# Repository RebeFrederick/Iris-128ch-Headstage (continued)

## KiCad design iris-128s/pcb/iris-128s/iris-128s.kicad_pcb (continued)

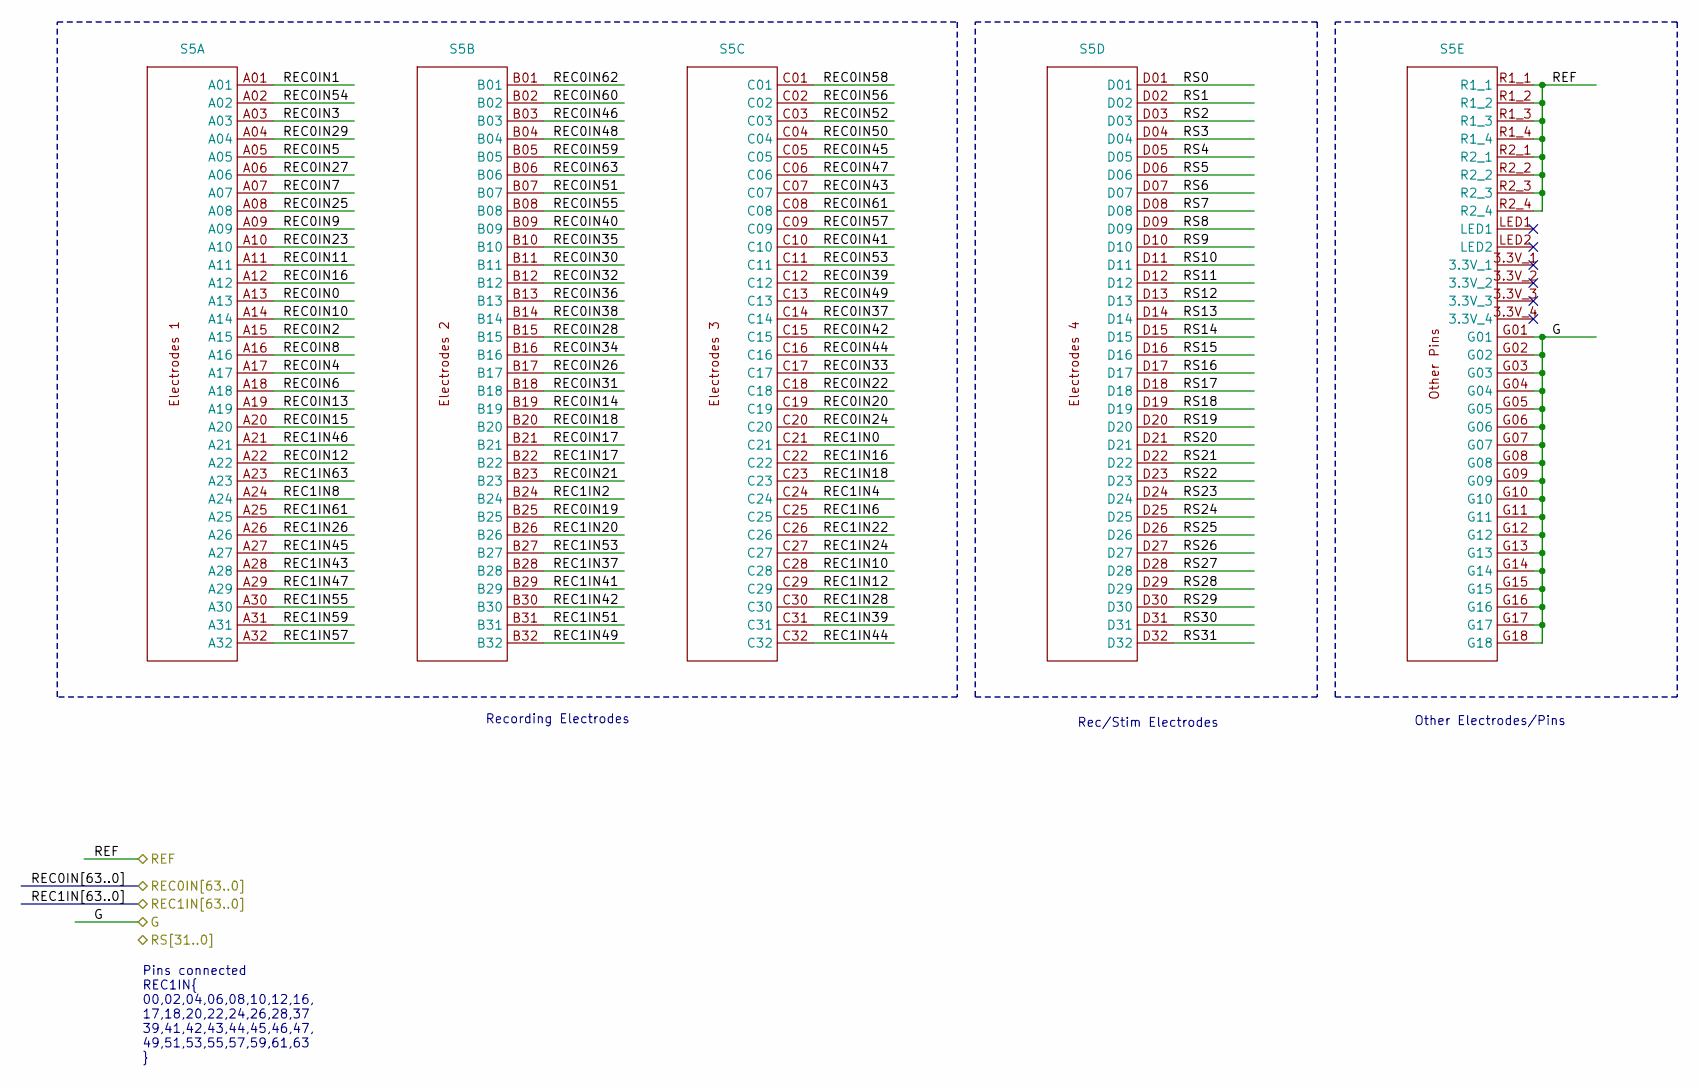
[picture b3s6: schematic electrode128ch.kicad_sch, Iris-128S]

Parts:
S5: SAMTEC_SEAM8-20-S02.0-X-08-3_Cereplex; MPN SEAM8-20-S02.0-S-08-3

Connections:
/REC0IN0: S5.A13; also elsewhere on the board
/REC0IN1: S5.A01; also elsewhere on the board
/REC0IN2: S5.A15; also elsewhere on the board
/REC0IN3: S5.A03; also elsewhere on the board
/REC0IN4: S5.A17; also elsewhere on the board
/REC0IN5: S5.A05; also elsewhere on the board
/REC0IN6: S5.A18; also elsewhere on the board
/REC0IN7: S5.A07; also elsewhere on the board
/REC0IN8: S5.A16; also elsewhere on the board
/REC0IN9: S5.A09; also elsewhere on the board
/REC0IN10: S5.A14; also elsewhere on the board
/REC0IN11: S5.A11; also elsewhere on the board
/REC0IN12: S5.A22; also elsewhere on the board
/REC0IN13: S5.A19; also elsewhere on the board
/REC0IN14: S5.B19; also elsewhere on the board
/REC0IN15: S5.A20; also elsewhere on the board
/REC0IN16: S5.A12; also elsewhere on the board
/REC0IN17: S5.B21; also elsewhere on the board
/REC0IN18: S5.B20; also elsewhere on the board
/REC0IN19: S5.B25; also elsewhere on the board
/REC0IN20: S5.C19; also elsewhere on the board
/REC0IN21: S5.B23; also elsewhere on the board
/REC0IN22: S5.C18; also elsewhere on the board
/REC0IN23: S5.A10; also elsewhere on the board
/REC0IN24: S5.C20; also elsewhere on the board
/REC0IN25: S5.A08; also elsewhere on the board
/REC0IN26: S5.B17; also elsewhere on the board
/REC0IN27: S5.A06; also elsewhere on the board
/REC0IN28: S5.B15; also elsewhere on the board
/REC0IN29: S5.A04; also elsewhere on the board
/REC0IN30: S5.B11; also elsewhere on the board
/REC0IN31: S5.B18; also elsewhere on the board
/REC0IN32: S5.B12; also elsewhere on the board
/REC0IN33: S5.C17; also elsewhere on the board
/REC0IN34: S5.B16; also elsewhere on the board
/REC0IN35: S5.B10; also elsewhere on the board
/REC0IN36: S5.B13; also elsewhere on the board
/REC0IN37: S5.C14; also elsewhere on the board
/REC0IN38: S5.B14; also elsewhere on the board
/REC0IN39: S5.C12; also elsewhere on the board
/REC0IN40: S5.B09; also elsewhere on the board
/REC0IN41: S5.C10; also elsewhere on the board
/REC0IN42: S5.C15; also elsewhere on the board
/REC0IN43: S5.C07; also elsewhere on the board
/REC0IN44: S5.C16; also elsewhere on the board
/REC0IN45: S5.C05; also elsewhere on the board
/REC0IN46: S5.B03; also elsewhere on the board
/REC0IN47: S5.C06; also elsewhere on the board
/REC0IN48: S5.B04; also elsewhere on the board
/REC0IN49: S5.C13; also elsewhere on the board
/REC0IN50: S5.C04; also elsewhere on the board
/REC0IN51: S5.B07; also elsewhere on the board
/REC0IN52: S5.C03; also elsewhere on the board
/REC0IN53: S5.C11; also elsewhere on the board
/REC0IN54: S5.A02; also elsewhere on the board
/REC0IN55: S5.B08; also elsewhere on the board
/REC0IN56: S5.C02; also elsewhere on the board
/REC0IN57: S5.C09; also elsewhere on the board
/REC0IN58: S5.C01; also elsewhere on the board
/REC0IN59: S5.B05; also elsewhere on the board
/REC0IN60: S5.B02; also elsewhere on the board
/REC0IN61: S5.C08; also elsewhere on the board
/REC0IN62: S5.B01; also elsewhere on the board
/REC0IN63: S5.B06; also elsewhere on the board
/REC1IN0: S5.C21; also elsewhere on the board
/REC1IN2: S5.B24; also elsewhere on the board
/REC1IN4: S5.C24; also elsewhere on the board
/REC1IN6: S5.C25; also elsewhere on the board
/REC1IN8: S5.A24; also elsewhere on the board
/REC1IN10: S5.C28; also elsewhere on the board
/REC1IN12: S5.C29; also elsewhere on the board
/REC1IN16: S5.C22; also elsewhere on the board
/REC1IN17: S5.B22; also elsewhere on the board
/REC1IN18: S5.C23; also elsewhere on the board
/REC1IN20: S5.B26; also elsewhere on the board
/REC1IN22: S5.C26; also elsewhere on the board
/REC1IN24: S5.C27; also elsewhere on the board
/REC1IN26: S5.A26; also elsewhere on the board
/REC1IN28: S5.C30; also elsewhere on the board
/REC1IN37: S5.B28; also elsewhere on the board
/REC1IN39: S5.C31; also elsewhere on the board
/REC1IN41: S5.B29; also elsewhere on the board
/REC1IN42: S5.B30; also elsewhere on the board
/REC1IN43: S5.A28; also elsewhere on the board
/REC1IN44: S5.C32; also elsewhere on the board
/REC1IN45: S5.A27; also elsewhere on the board
/REC1IN46: S5.A21; also elsewhere on the board
/REC1IN47: S5.A29; also elsewhere on the board
/REC1IN49: S5.B32; also elsewhere on the board
/REC1IN51: S5.B31; also elsewhere on the board
/REC1IN53: S5.B27; also elsewhere on the board
/REC1IN55: S5.A30; also elsewhere on the board
/REC1IN57: S5.A32; also elsewhere on the board
/REC1IN59: S5.A31; also elsewhere on the board
/REC1IN61: S5.A25; also elsewhere on the board
/REC1IN63: S5.A23; also elsewhere on the board
/REF_ELEC: S5.R1_1, S5.R1_2, S5.R1_3, S5.R1_4, S5.R2_1, S5.R2_2, S5.R2_3, S5.R2_4; also elsewhere on the board
/RS0: S5.D01; also elsewhere on the board
/RS1: S5.D02; also elsewhere on the board
/RS2: S5.D03; also elsewhere on the board
/RS3: S5.D04; also elsewhere on the board
/RS4: S5.D05; also elsewhere on the board
/RS5: S5.D06; also elsewhere on the board
/RS6: S5.D07; also elsewhere on the board
/RS7: S5.D08; also elsewhere on the board
/RS8: S5.D09; also elsewhere on the board
/RS9: S5.D10; also elsewhere on the board
/RS10: S5.D11; also elsewhere on the board
/RS11: S5.D12; also elsewhere on the board
/RS12: S5.D13; also elsewhere on the board
/RS13: S5.D14; also elsewhere on the board
/RS14: S5.D15; also elsewhere on the board
/RS15: S5.D16; also elsewhere on the board
/RS16: S5.D17; also elsewhere on the board
/RS17: S5.D18; also elsewhere on the board
/RS18: S5.D19; also elsewhere on the board
/RS19: S5.D20; also elsewhere on the board
/RS20: S5.D21; also elsewhere on the board
/RS21: S5.D22; also elsewhere on the board
/RS22: S5.D23; also elsewhere on the board
/RS23: S5.D24; also elsewhere on the board
/RS24: S5.D25; also elsewhere on the board
/RS25: S5.D26; also elsewhere on the board
/RS26: S5.D27; also elsewhere on the board
/RS27: S5.D28; also elsewhere on the board
/RS28: S5.D29; also elsewhere on the board
/RS29: S5.D30; also elsewhere on the board
/RS30: S5.D31; also elsewhere on the board
/RS31: S5.D32; also elsewhere on the board
GND1: S5.G01, S5.G02, S5.G03, S5.G04, S5.G05, S5.G06, S5.G07, S5.G08, S5.G09, S5.G10, S5.G11, S5.G12, S5.G13, S5.G14, S5.G15, S5.G16, S5.G17, S5.G18; also elsewhere on the board

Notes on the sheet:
Pins connected REC1IN{ 00,02,04,06,08,10,12,16, 17,18,20,22,24,26,28,37 39,41,42,43,44,45,46,47, 49,51,53,55,57,59,61,63 }
Rec/Stim Electrodes
Other Electrodes/Pins
Recording Electrodes

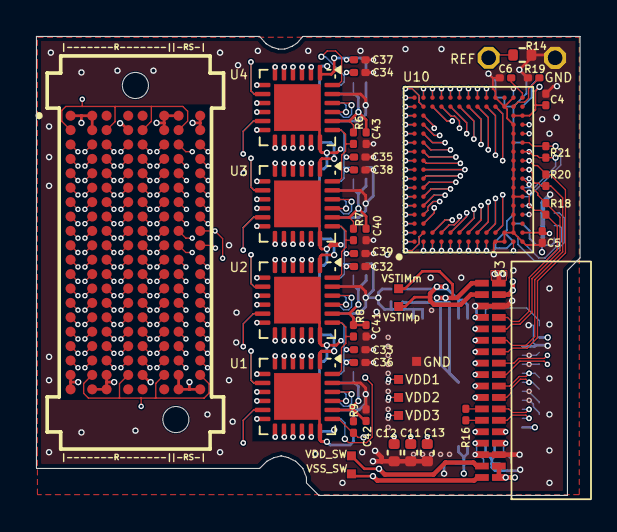
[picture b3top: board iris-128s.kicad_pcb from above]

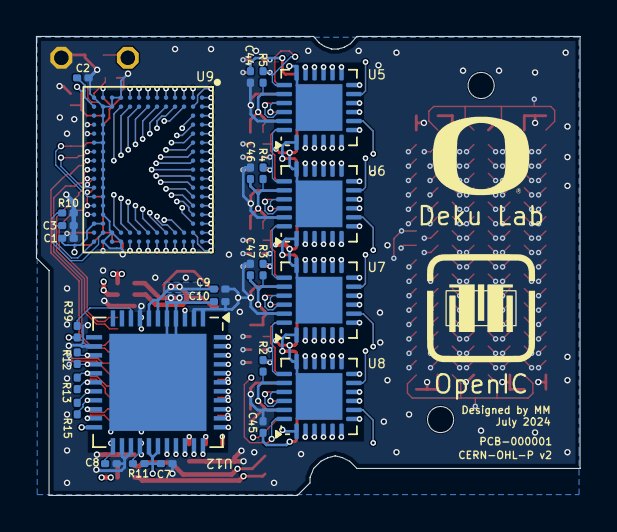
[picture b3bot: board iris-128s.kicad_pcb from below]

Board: 8 copper layers, 30.2 x 25.5 mm, 72 parts (27 on the bottom side), 223 nets.

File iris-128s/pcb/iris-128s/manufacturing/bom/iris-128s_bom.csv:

Reference,Value,Qty,DNP,MPN,Manufacturer
"C1,C2,C4,C5,C7,C9,C10,C32,C33,C34,C35,C36,C37,C38,C39,C40,C41,C42,C43,C44,C45,C46,C47",100n,23,,C0603X5R1C104K030BC,TDK
"C3,C6,C8",10n,3,,GRM033R61C103KA12D,Murata Electronics
"C11,C12,C13",4.7u,3,,KGM05CR51C475MH,Kyocera AVX
"GND1,REF0,TP1,TP2,TP3,TP4,TP5,TP6,TP7,TP8",-- mixed values --,10,,~,
"R2,R3,R4,R5,R6,R7,R8,R9",20k,8,,RC0201FR-0720KL,Yageo
"R10,R14,R19",0,3,DNP,,
"R11,R39",1,2,,RC0201FR-071RL,Yageo
"R12,R13,R15,R16,R18,R20,R21",100,7,,RC0201FR-07100RL,Yageo
S3,~,1,,A79024-001,Omnetics
S5,~,1,,SEAM8-20-S02.0-S-08-3,Samtec
"U1,U2,U3,U4,U5,U6,U7,U8",~,8,,  ADGS5414BCPZ,ADI
"U9,U10",~,2,,RHD2164,Intan Technologies
U12,~,1,,RHS2116,Intan Technologies

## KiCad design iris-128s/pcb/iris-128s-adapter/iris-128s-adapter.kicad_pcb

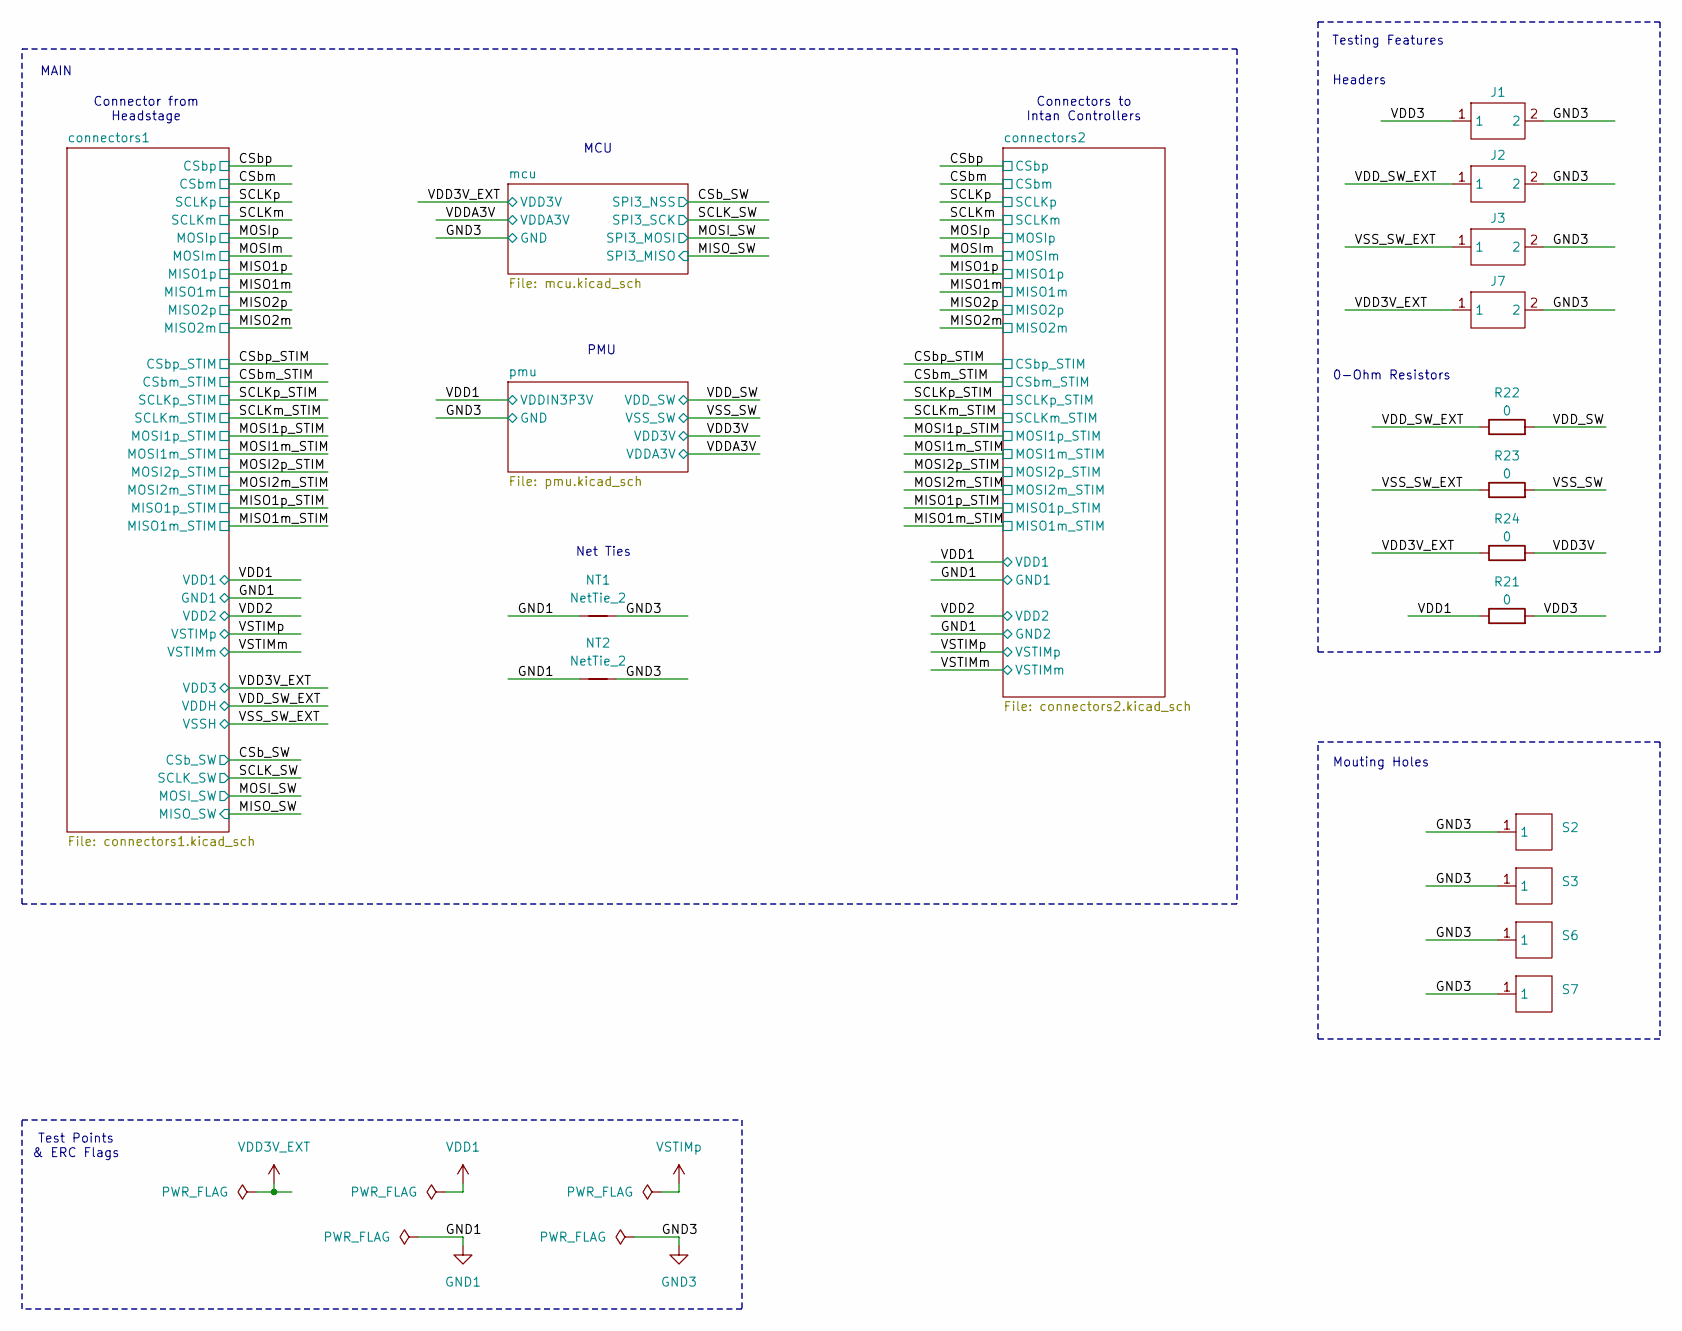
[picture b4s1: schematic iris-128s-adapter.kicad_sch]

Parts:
J1, J2, J3, J7: TLW-102-06-G-S; MPN TLW-102-06-G-S
NT1, NT2: NetTie_2; NetTie-2_SMD_Pad0.5mm; MPN None
R21, R22, R23, R24: 0; R_0402_1005Metric; MPN RC0402JR-070RL
S2, S3, S6, S7: MOUNTING_HOLE-PAD-0.1IN; MPN None

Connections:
/VDD3: J1.1, R21.2
/VDD3V: R24.2; also elsewhere on the board
/VDD_SW: R22.2; also elsewhere on the board
/VDD_SW_EXT: J2.1, R22.1; also elsewhere on the board
/VSS_SW: R23.2; also elsewhere on the board
/VSS_SW_EXT: J3.1, R23.1; also elsewhere on the board
GND1: NT1.1, NT2.1; also elsewhere on the board
GND3: J1.2, J2.2, J3.2, J7.2, NT1.2, NT2.2, S2.1, S3.1, S6.1, S7.1; also elsewhere on the board
VDD1: R21.1; also elsewhere on the board
VDD3V_EXT: J7.1, R24.1; also elsewhere on the board

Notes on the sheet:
Net Ties
MAIN
Connector from Headstage
Test Points & ERC Flags
Mouting Holes
Headers
MCU
PMU
0-Ohm Resistors
Connectors to Intan Controllers
Testing Features

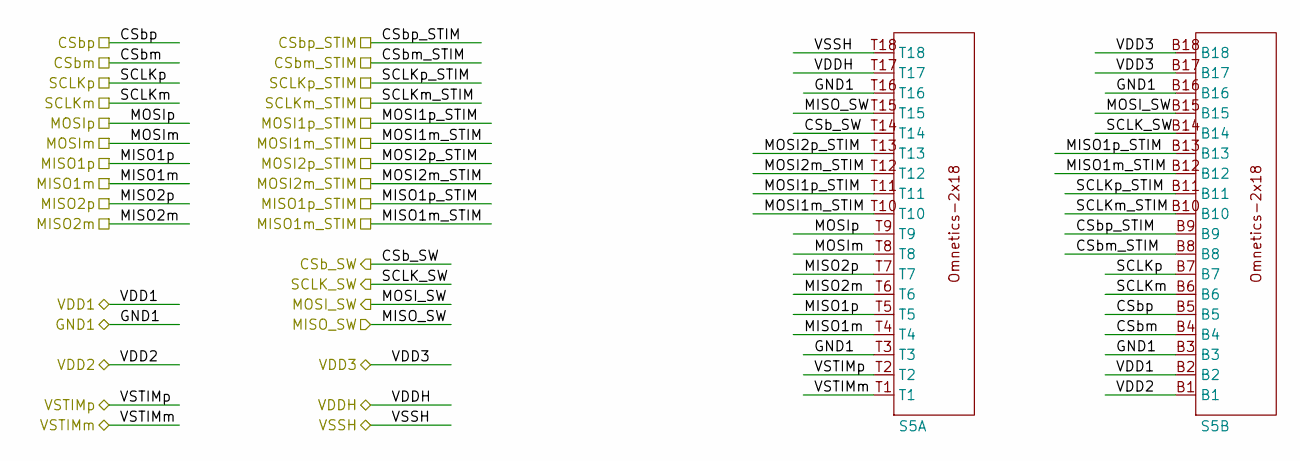
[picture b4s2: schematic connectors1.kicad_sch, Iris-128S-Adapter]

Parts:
S5: OMNETICS-A79024-001; MPN A79024-001

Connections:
/CSb_SW: S5.T14; also elsewhere on the board
/CSbm: S5.B4; also elsewhere on the board
/CSbm_STIM: S5.B8; also elsewhere on the board
/CSbp: S5.B5; also elsewhere on the board
/CSbp_STIM: S5.B9; also elsewhere on the board
/MISO1m: S5.T4; also elsewhere on the board
/MISO1m_STIM: S5.B12; also elsewhere on the board
/MISO1p: S5.T5; also elsewhere on the board
/MISO1p_STIM: S5.B13; also elsewhere on the board
/MISO2m: S5.T6; also elsewhere on the board
/MISO2p: S5.T7; also elsewhere on the board
/MISO_SW: S5.T15; also elsewhere on the board
/MOSI1m_STIM: S5.T10; also elsewhere on the board
/MOSI1p_STIM: S5.T11; also elsewhere on the board
/MOSI2m_STIM: S5.T12; also elsewhere on the board
/MOSI2p_STIM: S5.T13; also elsewhere on the board
/MOSI_SW: S5.B15; also elsewhere on the board
/MOSIm: S5.T8; also elsewhere on the board
/MOSIp: S5.T9; also elsewhere on the board
/SCLK_SW: S5.B14; also elsewhere on the board
/SCLKm: S5.B6; also elsewhere on the board
/SCLKm_STIM: S5.B10; also elsewhere on the board
/SCLKp: S5.B7; also elsewhere on the board
/SCLKp_STIM: S5.B11; also elsewhere on the board
/VDD2: S5.B1; also elsewhere on the board
/VDD_SW_EXT: S5.T17; also elsewhere on the board
/VSS_SW_EXT: S5.T18; also elsewhere on the board
/VSTIMm: S5.T1; also elsewhere on the board
GND1: S5.B3, S5.B16, S5.T3, S5.T16; also elsewhere on the board
VDD1: S5.B2; also elsewhere on the board
VDD3V_EXT: S5.B17, S5.B18; also elsewhere on the board
VSTIMp: S5.T2; also elsewhere on the board

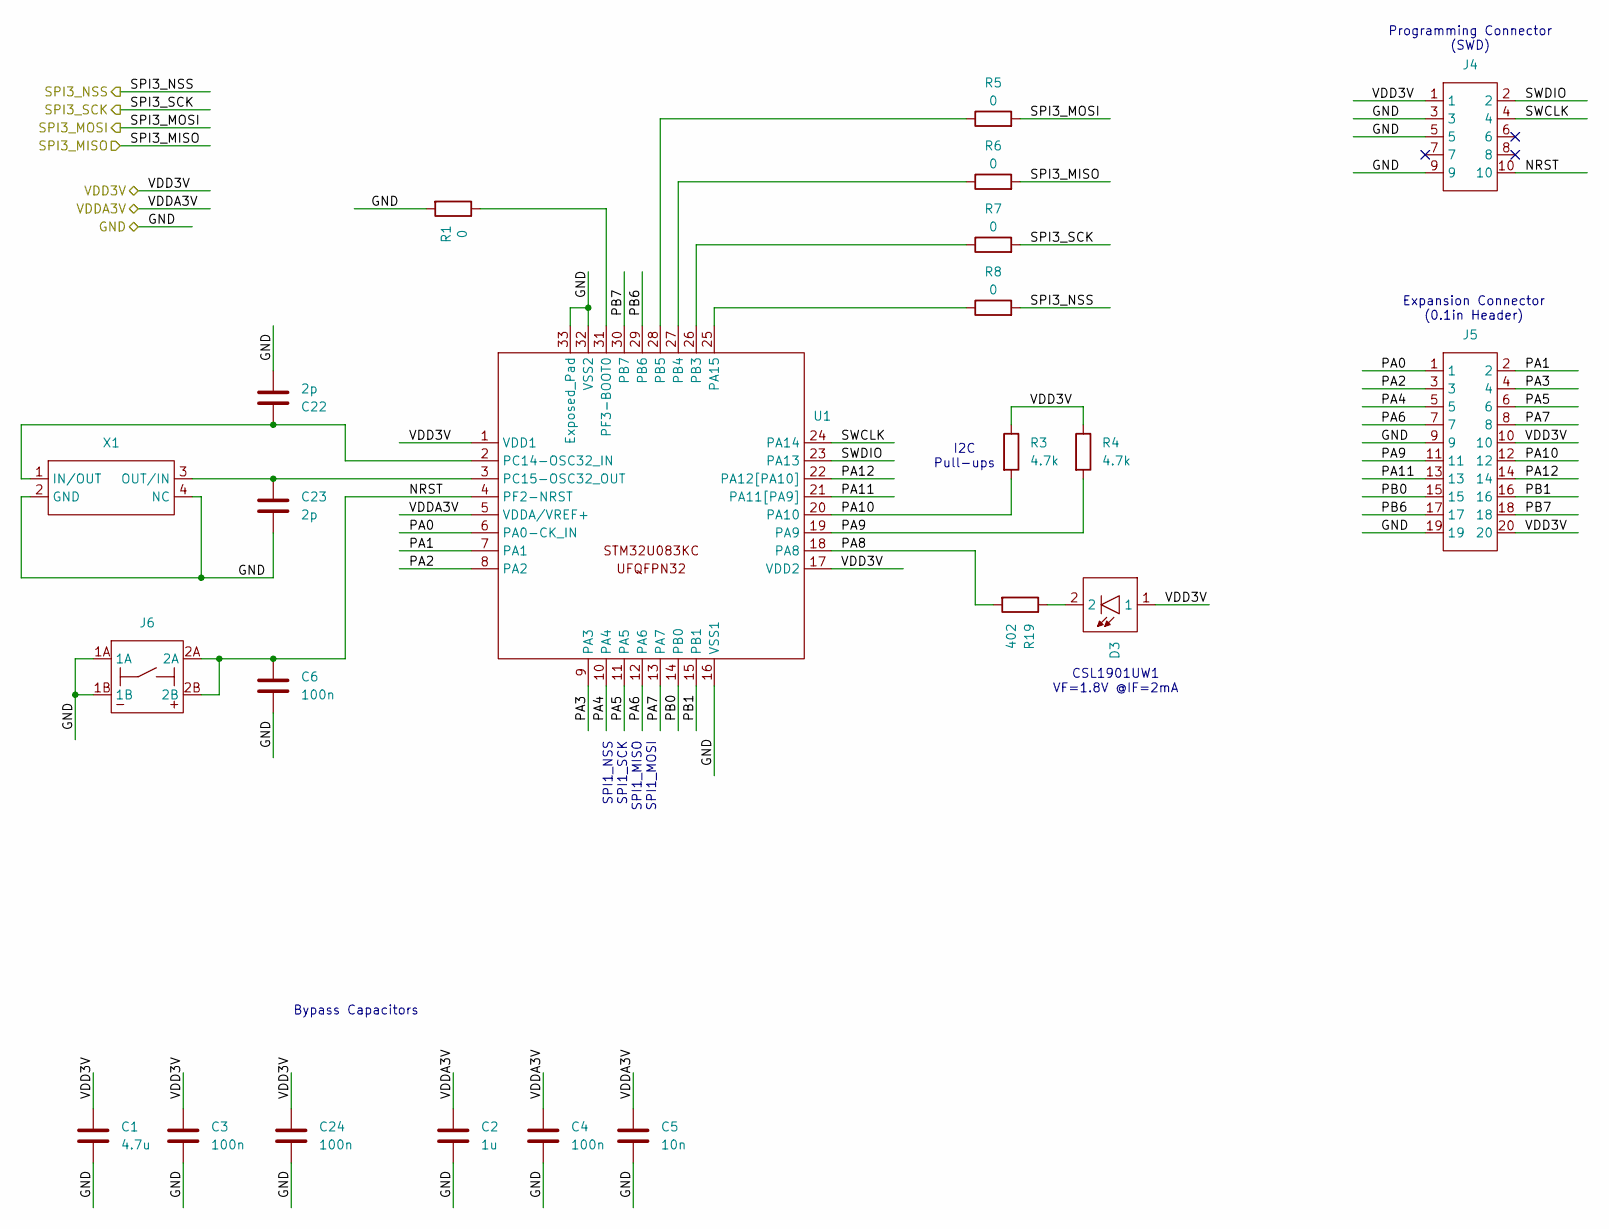
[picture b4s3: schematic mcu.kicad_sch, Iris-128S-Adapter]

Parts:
C1: 4.7u; C_0402_1005Metric; MPN KGM05CR51C475MH
C2: 1u; C_0201_0603Metric; MPN GRM033R61C105ME15D
C3, C4, C6, C24: 100n; C_0201_0603Metric; MPN C0603X5R1C104K030BC
C5: 10n; C_0201_0603Metric; MPN GRM033R61C103KA12D
C22, C23: 2p; C_0201_0603Metric; MPN GJM0335C1E2R0WB01D
D3: ROHM-LED-0603; MPN CSL1901UW1
J4: SMD-ARM10-10_2x5_P0.05in; MPN FTSH-105-01-L-DV-K
J5: SLW-110-01-G-D; MPN SLW-110-01-G-D
J6: BOURNES-PUSHBUTTON-7914G-1-000; MPN 7914G-1-000
R1: 0; R_0201_0603Metric; MPN RC0201FR-070RL
R3, R4: 4.7k; R_0201_0603Metric; MPN RC0201FR-074K7L
R5, R6, R7, R8: 0; R_0402_1005Metric; MPN RC0402JR-070RL
R19: 402; R_0402_1005Metric; MPN RCS0402402RFKED
U1: UFQFPN-32-1EP_5x5mm_P0.5mm_EP3.6x3.6mm; MPN STM32U083KCU6
X1: CRYSTAL-ECS-ECX-1210B-32KHZ; MPN ECS-.327-6-1210B-N-TR

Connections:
/CSb_SW: R8.2; also elsewhere on the board
/MISO_SW: R6.2; also elsewhere on the board
/MOSI_SW: R5.2; also elsewhere on the board
/SCLK_SW: R7.2; also elsewhere on the board
/VDDA3V: C2.1, C4.1, C5.1, U1.5 (VDDA/VREF+); also elsewhere on the board
/mcu/NRST: C6.1, J4.10, J6.2A, J6.2B, U1.4 (PF2-NRST)
/mcu/PA0: J5.1, U1.6 (PA0-CK_IN)
/mcu/PA1: J5.2, U1.7 (PA1)
/mcu/PA2: J5.3, U1.8 (PA2)
/mcu/PA3: J5.4, U1.9 (PA3)
/mcu/PA4: J5.5, U1.10 (PA4)
/mcu/PA5: J5.6, U1.11 (PA5)
/mcu/PA6: J5.7, U1.12 (PA6)
/mcu/PA7: J5.8, U1.13 (PA7)
/mcu/PA8: R19.2, U1.18 (PA8)
/mcu/PA9: J5.11, R4.2, U1.19 (PA9)
/mcu/PA10: J5.12, R3.2, U1.20 (PA10)
/mcu/PA11: J5.13, U1.21 (PA11[PA9])
/mcu/PA12: J5.14, U1.22 (PA12[PA10])
/mcu/PB0: J5.15, U1.14 (PB0)
/mcu/PB1: J5.16, U1.15 (PB1)
/mcu/PB6: J5.17, U1.29 (PB6)
/mcu/PB7: J5.18, U1.30 (PB7)
/mcu/SWCLK: J4.4, U1.24 (PA14)
/mcu/SWDIO: J4.2, U1.23 (PA13)
GND3: C1.2, C2.2, C3.2, C4.2, C5.2, C6.2, C22.2, C23.2, C24.2, J4.3, J4.5, J4.9, J5.9, J5.19, J6.1A, J6.1B, R1.2, U1.16 (VSS1), U1.32 (VSS2), U1.33 (Exposed_Pad), X1.2 (GND), X1.4 (NC); also elsewhere on the board
unnamed: D3.2, R19.1
unnamed: R8.1, U1.25 (PA15)
unnamed: R7.1, U1.26 (PB3)
unnamed: R6.1, U1.27 (PB4)
unnamed: R5.1, U1.28 (PB5)
unnamed: C22.1, U1.2 (PC14-OSC32_IN), X1.1 (IN/OUT)
unnamed: C23.1, U1.3 (PC15-OSC32_OUT), X1.3 (OUT/IN)
unnamed: R1.1, U1.31 (PF3-BOOT0)
VDD3V_EXT: C1.1, C3.1, C24.1, D3.1, J4.1, J5.10, J5.20, R3.1, R4.1, U1.1 (VDD1), U1.17 (VDD2); also elsewhere on the board

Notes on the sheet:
I2C Pull-ups
SPI1_NSS SPI1_SCK SPI1_MISO SPI1_MOSI
CSL1901UW1 VF=1.8V @IF=2mA
Expansion Connector (0.1in Header)
Programming Connector (SWD)
Bypass Capacitors

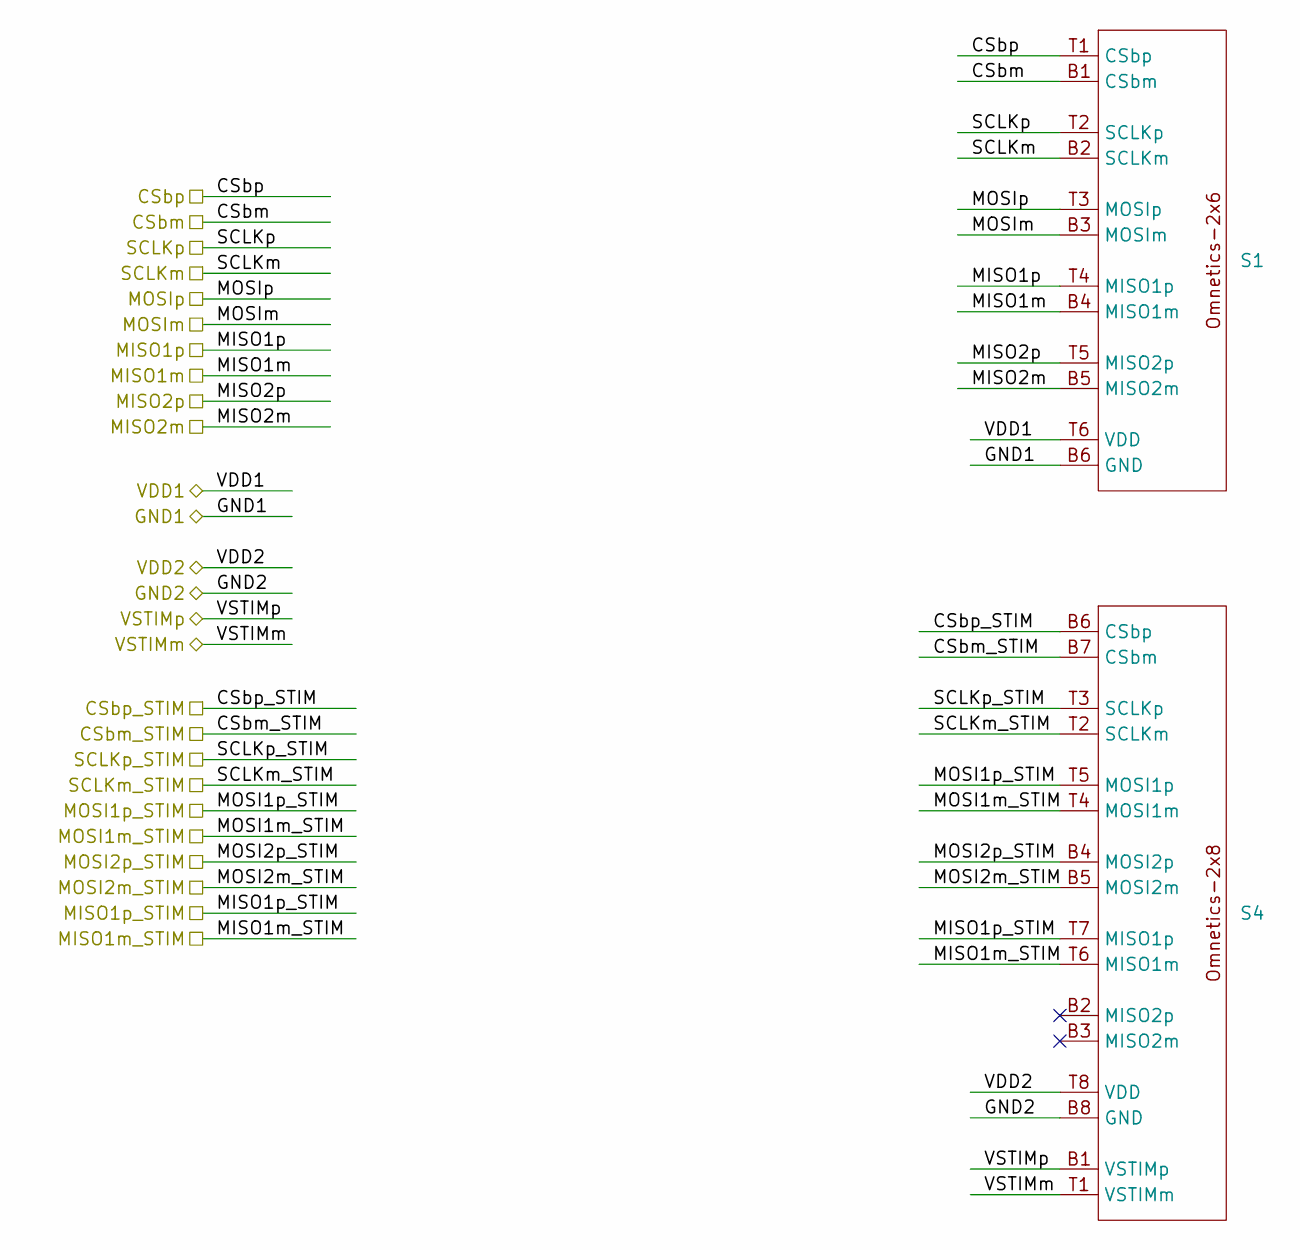
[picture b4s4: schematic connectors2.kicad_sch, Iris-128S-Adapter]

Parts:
S1: OMNETICS_PZN-12-AA; MPN A79623-001
S4: OMNETICS_PZN-16-AA; MPN A79633-001

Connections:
/CSbm: S1.B1 (CSbm); also elsewhere on the board
/CSbm_STIM: S4.B7 (CSbm); also elsewhere on the board
/CSbp: S1.T1 (CSbp); also elsewhere on the board
/CSbp_STIM: S4.B6 (CSbp); also elsewhere on the board
/MISO1m: S1.B4 (MISO1m); also elsewhere on the board
/MISO1m_STIM: S4.T6 (MISO1m); also elsewhere on the board
/MISO1p: S1.T4 (MISO1p); also elsewhere on the board
/MISO1p_STIM: S4.T7 (MISO1p); also elsewhere on the board
/MISO2m: S1.B5 (MISO2m); also elsewhere on the board
/MISO2p: S1.T5 (MISO2p); also elsewhere on the board
/MOSI1m_STIM: S4.T4 (MOSI1m); also elsewhere on the board
/MOSI1p_STIM: S4.T5 (MOSI1p); also elsewhere on the board
/MOSI2m_STIM: S4.B5 (MOSI2m); also elsewhere on the board
/MOSI2p_STIM: S4.B4 (MOSI2p); also elsewhere on the board
/MOSIm: S1.B3 (MOSIm); also elsewhere on the board
/MOSIp: S1.T3 (MOSIp); also elsewhere on the board
/SCLKm: S1.B2 (SCLKm); also elsewhere on the board
/SCLKm_STIM: S4.T2 (SCLKm); also elsewhere on the board
/SCLKp: S1.T2 (SCLKp); also elsewhere on the board
/SCLKp_STIM: S4.T3 (SCLKp); also elsewhere on the board
/VDD2: S4.T8 (VDD); also elsewhere on the board
/VSTIMm: S4.T1 (VSTIMm); also elsewhere on the board
GND1: S1.B6 (GND), S4.B8 (GND); also elsewhere on the board
VDD1: S1.T6 (VDD); also elsewhere on the board
VSTIMp: S4.B1 (VSTIMp); also elsewhere on the board

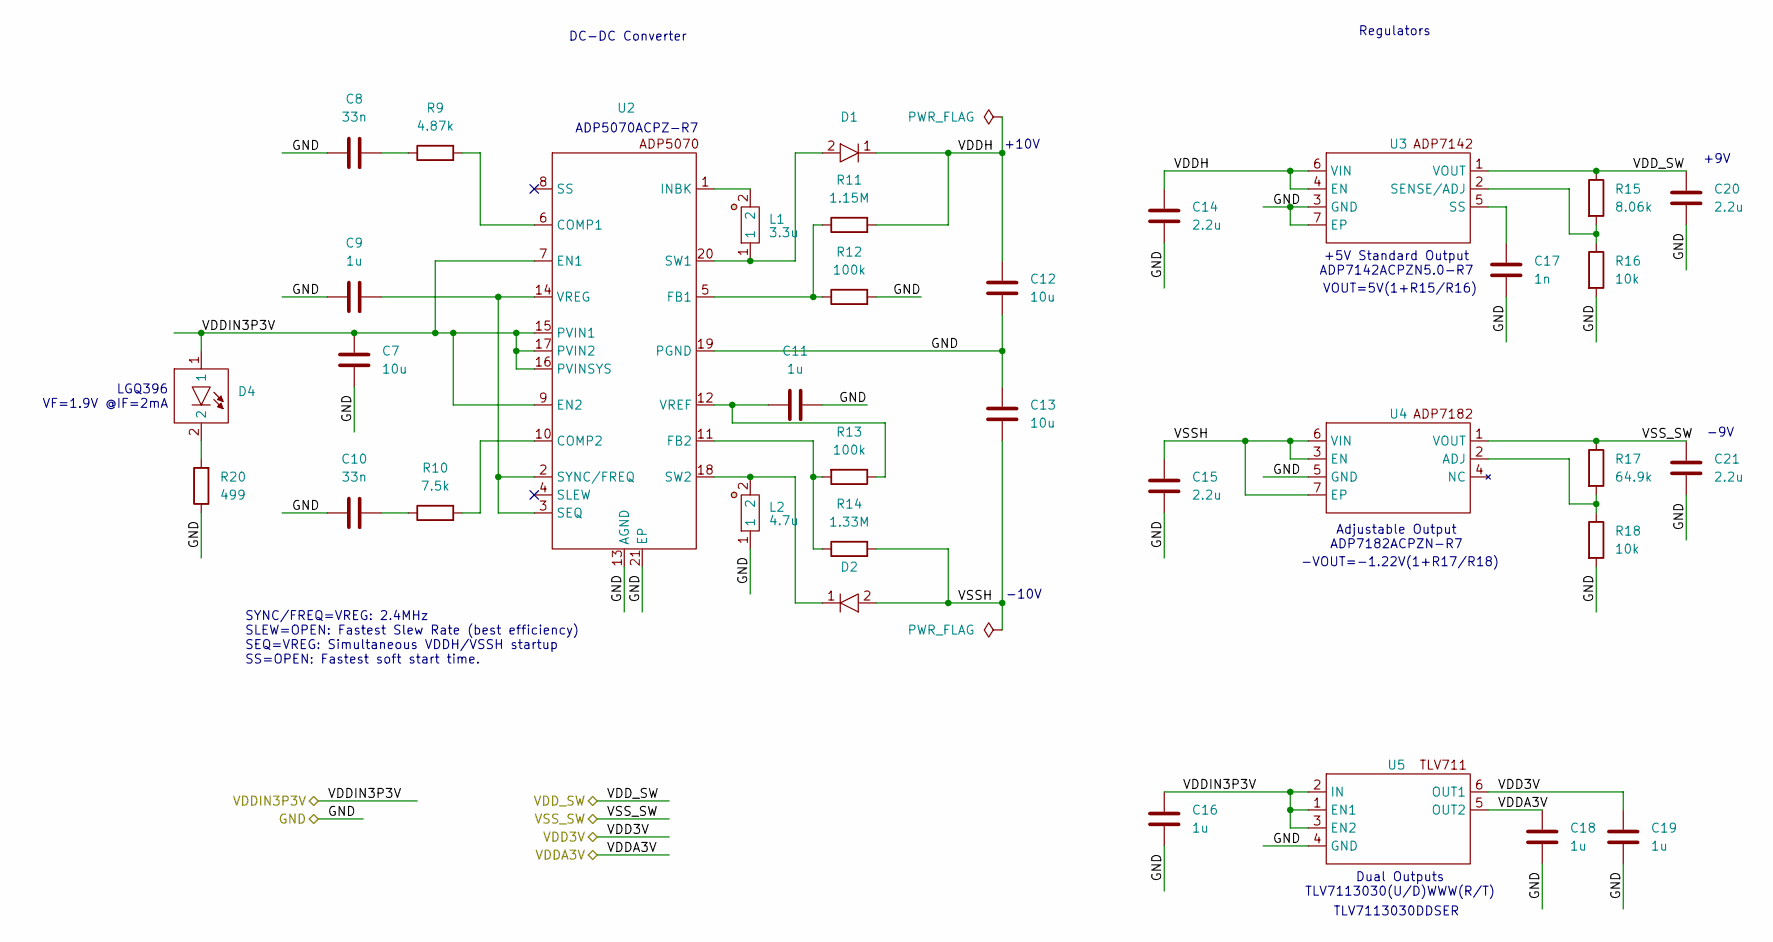
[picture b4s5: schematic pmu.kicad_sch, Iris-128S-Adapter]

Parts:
C7, C12, C13: 10u; C_0603_1608Metric; MPN GRM188R61E106KA73D
C8, C10: 33n; C_0201_0603Metric; MPN GRM033R61C333KE84D
C9, C11, C16, C18, C19: 1u; C_0201_0603Metric; MPN GRM033R61C105ME15D
C14, C15, C20, C21: 2.2u; C_0201_0603Metric; MPN GRM035R61C225ME01D
C17: 1n; C_0201_0603Metric; MPN GRM033R61E102KA01J
D1, D2: X3-WLB1006-2; MPN SDM05U20CSP-7
D4: OSRAM-LED-0603; MPN LGQ396
L1: 3.3u; SMD-0808; MPN XFL2006-332MEC
L2: 4.7u; SMD-0808; MPN XFL2006-472MEC
R9: 4.87k; R_0201_0603Metric; MPN RC0201FR-074K87L
R10: 7.5k; R_0201_0603Metric; MPN RC0201FR-077K5L
R11: 1.15M; R_0201_0603Metric; MPN CRCW02011M15FNED
R12, R13: 100k; R_0201_0603Metric; MPN RC0201FR-07100KL
R14: 1.33M; R_0201_0603Metric; MPN CRCW02011M33FNED
R15: 8.06k; R_0201_0603Metric; MPN RC0201FR-078K06L
R16, R18: 10k; R_0201_0603Metric; MPN RC0201FR-0710KL
R17: 64.9k; R_0201_0603Metric; MPN RC0201FR-0764K9L
R20: 499; R_0402_1005Metric; MPN RCS0402499RFKED
U2: LFCSP-20-1EP_4mmx4mm_P0.5mm_EP2.6mm; MPN ADP5070ACPZ-R7
U3: LFCSP-6-1EP_2mmx2mm_P0.65mm_EP1.6mmx1mm; MPN ADP7142ACPZN5.0-R7
U4: LFCSP-6-1EP_2mmx2mm_P0.65mm_EP1.6mmx1mm; MPN ADP7182ACPZN-R7
U5: WSON-6_1.5mmx1.5mm_P0.5mm; MPN TLV7113030DDSER

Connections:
/VDD3V: C19.1, U5.6 (OUT1); also elsewhere on the board
/VDDA3V: C18.1, U5.5 (OUT2); also elsewhere on the board
/VDD_SW: C20.1, R15.1, U3.1 (VOUT); also elsewhere on the board
/VSS_SW: C21.1, R17.1, U4.1 (VOUT); also elsewhere on the board
/pmu/VDDH: C12.1, C14.1, D1.1, R11.2, U3.4 (EN), U3.6 (VIN)
/pmu/VSSH: C13.2, C15.1, D2.2, R14.2, U4.3 (EN), U4.6 (VIN), U4.7 (EP)
GND3: C7.2, C8.1, C9.1, C10.1, C11.2, C12.2, C13.1, C14.2, C15.2, C16.2, C17.2, C18.2, C19.2, C20.2, C21.2, L2.1, R12.2, R16.2, R18.2, R20.1, U2.13 (AGND), U2.19 (PGND), U2.21 (EP), U3.3 (GND), U3.7 (EP), U4.5 (GND), U5.4 (GND); also elsewhere on the board
unnamed: C8.2, R9.1
unnamed: C10.2, R10.1
unnamed: D4.2, R20.2
unnamed: R9.2, U2.6 (COMP1)
unnamed: R10.2, U2.10 (COMP2)
unnamed: R11.1, R12.1, U2.5 (FB1)
unnamed: R13.2, R14.1, U2.11 (FB2)
unnamed: L1.2, U2.1 (INBK)
unnamed: C9.2, U2.2 (SYNC/FREQ), U2.3 (SEQ), U2.14 (VREG)
unnamed: D1.2, L1.1, U2.20 (SW1)
unnamed: D2.1, L2.2, U2.18 (SW2)
unnamed: C11.1, R13.1, U2.12 (VREF)
unnamed: R15.2, R16.1, U3.2 (SENSE/ADJ)
unnamed: C17.1, U3.5 (SS)
unnamed: R17.2, R18.1, U4.2 (ADJ)
VDD1: C7.1, C16.1, D4.1, U2.7 (EN1), U2.9 (EN2), U2.15 (PVIN1), U2.16 (PVINSYS), U2.17 (PVIN2), U5.1 (EN1), U5.2 (IN), U5.3 (EN2); also elsewhere on the board

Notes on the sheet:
Regulators
LGQ396 VF=1.9V @IF=2mA
-9V
DC-DC Converter
-10V
Adjustable Output ADP7182ACPZN-R7
ADP5070ACPZ-R7
Dual Outputs TLV7113030(U/D)WWW(R/T)
+9V
+5V Standard Output ADP7142ACPZN5.0-R7
SYNC/FREQ=VREG: 2.4MHz SLEW=OPEN: Fastest Slew Rate (best efficiency) SEQ=VREG: Simultaneous VDDH/VSSH startup SS=OPEN: Fastest soft start time.
TLV7113030DDSER
+10V
VOUT=5V(1+R15/R16)
-VOUT=-1.22V(1+R17/R18)
